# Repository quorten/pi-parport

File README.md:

## pi-parport

This is a Raspberry Pi HAT that implements a PC-style parallel port.
GPIO pins are organized as data, status, and control registers.
The HAT includes a buffer chip that converts from the GPIB 3V3 logic
to signals that conform to IEEE 1284.  A 26 pin IDC header on the
board connects to your DB25 connector.  A `parport-gpio` driver and
device tree overlay integrate the HAT with the Linux parport driver stack.

### Why?

I wanted to use a parallel port based cooled astronomy camera,
but preferred to use the compact and low-power Raspberry Pi
over a PC at the telescope.  Parallel ports are simple devices.
Why not build one?

### What works?

See [wiki](https://github.com/worlickwerx/pi-parport/wiki) for notes on some
devices, and please share your experience if you try something new.

The following limitations of this implementation may affect software and
hardware that uses the parallel port:
1) The software cannot directly read and write the x86 port addresses,
as was the custom early on.  In user space, software must use the ppdev
ioctl interface.  In the kernel, software must use the (generic)
`struct parport` operations.
2) The GPIO multiplexing/de-multiplexing and/or system call access may
impact the direct-access latency assumed by some bit-banged drivers.
On a Pi 3, user space code can toggle a parallel port line at about 250 kHz.
3) Bidirectional control pins are not currently supported.  There are
alternatives to the current buffer chip that would support this, but they
require a slightly more complicated circuit.

### Why not use a USB Parallel Port?

Many USB parallel port devices appear to Linux as a USB printer, bypassing
the parport driver stack.  If your application is a printer, go for it.

### Building the driver

For convenience, the generic parport code is duplicated in this repo,
since the Raspberry Pi Foundation does not ship the compiled modules
in the `raspberrypi-kernel` package (at least in old Raspbian
versions).  If you are intending to use a specific old version of
Raspbian, there is the shell script `get_parport_src.sh` to assist
you in getting the code from that particular version.

Clone this repo, then run the following with `${TOPDIR}` representing the
top level directory of the cloned repo:
```console
$ sudo apt install build-essential raspberrypi-kernel-headers
$ cd ${TOPDIR}/driver
$ make
make -C /lib/modules/4.19.75-v7+/build M=${TOPDIR}/driver modules
make[1]: Entering directory '/usr/src/linux-headers-4.19.75-v7+'
  CC [M]  ${TOPDIR}/driver/parport/share.o
  CC [M]  ${TOPDIR}/driver/parport/ieee1284.o
  CC [M]  ${TOPDIR}/driver/parport/ieee1284_ops.o
  CC [M]  ${TOPDIR}/driver/parport/procfs.o
  CC [M]  ${TOPDIR}/driver/parport/daisy.o
  CC [M]  ${TOPDIR}/driver/parport/probe.o
  LD [M]  ${TOPDIR}/driver/parport/parport.o
  CC [M]  ${TOPDIR}/driver/parport/lp.o
  CC [M]  ${TOPDIR}/driver/parport/ppdev.o
  CC [M]  ${TOPDIR}/driver/parport_gpio.o
  Building modules, stage 2.
  MODPOST 4 modules
  CC      ${TOPDIR}/driver/parport/lp.mod.o
  LD [M]  ${TOPDIR}/driver/parport/lp.ko
  CC      ${TOPDIR}/driver/parport/parport.mod.o
  LD [M]  ${TOPDIR}/driver/parport/parport.ko
  CC      ${TOPDIR}/driver/parport/ppdev.mod.o
  LD [M]  ${TOPDIR}/driver/parport/ppdev.ko
  CC      ${TOPDIR}/driver/parport_gpio.mod.o
  LD [M]  ${TOPDIR}/driver/parport_gpio.ko
make[1]: Leaving directory '/usr/src/linux-headers-4.19.75-v7+'
```

### Installing the Device Tree Overlay

The device tree overlay maps specific GPIO pins to their functions in
the driver.  This must be compiled and loaded:
```console
$ cd ${TOPDIR}/dts
$ make
$ sudo make install
```
The ID EEPROM stores the name of the DT Overlay to use, and the
corresponding DT Overlay will be automatically loaded on boot.  If you
will not be using an ID EEPROM, then add the following line to
`/boot/config.txt`:
```
dtoverlay=parport-gpio
```
The default drive mode of the parallel port output pins is
"totem-pole" mode, which means that a high current source is provided
for both logic level 1 and 0.  If you wish logic level 1 to be a low
current source provided by pull-up resistors, i.e. "open-drain" mode,
then you can set the following DT Overlay parameter:
```
dtoverlay=parport-gpio,hd=0
```
Note that if you are using an EEPROM, you will have to include the
full DT Overlay data within your EEPROM since you cannot simply
specify a parameter when loading by that method.

Then reboot the pi to pick up the new config.

### Installing the Modules

Install the modules to allow Linux Device Tree to automatically load
them.
```console
$ cd ${TOPDIR}/driver
$ sudo make install
```
Note that only the `parport` and `parport_gpio` base modules will
autoload, the `ppdev` and `lp` modules will still need to be specified
in `/etc/modules` or otherwise.  Also, note that you will need to
rebuild and reinstall the modules when you update your kernel version.

### Loading the Modules

If you did not install the modules, after rebooting, load the base
modules like this:
```console
$ cd ${TOPDIR}
$ sudo insmod driver/parport/parport.ko
$ sudo insmod driver/parport_gpio.ko
```
You'll see the port announce itself on the console:
```console
[4425200.988400] parport-gpio ppgpio@0: data on pins [22,23,24,10,25,9,8,11]
[4425200.988412] parport-gpio ppgpio@0: status on pins [18,17,4,3,2]
[4425200.988422] parport-gpio ppgpio@0: control on pins [26,19,6,13]
[4425200.988430] parport-gpio ppgpio@0: hd on pin 20
[4425200.988438] parport-gpio ppgpio@0: dir on pin 21
```
If you wish to set up a parallel printer:
```console
$ sudo insmod parport/lp.ko
```
If you wish to run user-space programs that use the parallel port:
```console
$ sudo insmod parport/ppdev.ko
```

### hardware

The latest hardware includes an ID EEPROM to conform with the
[Raspberry Pi HAT Specification](https://github.com/raspberrypi/hats),
and was designed with [KiCAD](https://www.kicad.org/).
As with the previous versions, the
[SN74LVC161284 19-bit bus interface with 3-state outputs](http://www.ti.com/product/SN74LVC161284) takes care of buffering and line conditioning.

Version 4 is shared on
[OSHPARK](https://oshpark.com/shared_projects/0Ioh20Gk).
See the [Bill of Materials](hardware/v4/BOM.md) for parts to place on
the board.

Populating the EEPROM and associated components on a board you're making
yourself is optional.

Check out the [test](test/) directory for some simple "smoke tests"
on your assembled pi-parport board before attaching your more
expensive equipment.

Schematics and design files for [previous versions](hardware/)
are still available for reference.

### Release

Share and enjoy!

#### Software License

SPDX-License-Identifier: GPL-2.0-or-later

#### Hardware License

SPDX-License-Identifier: CERN-OHL-1.2

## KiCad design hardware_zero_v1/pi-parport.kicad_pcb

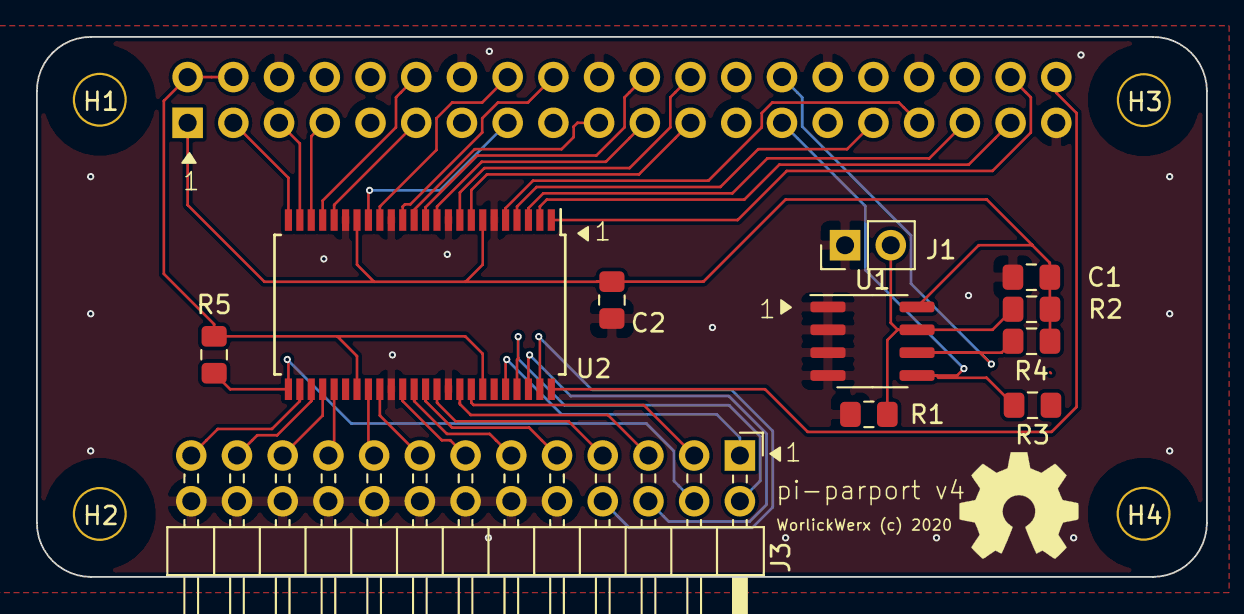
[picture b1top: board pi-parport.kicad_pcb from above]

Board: 2 copper layers, 65.0 x 30.0 mm, 16 parts (1 on the bottom side), 42 nets.

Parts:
C1, C2: 100nF; C_0805_2012Metric_Pad1.15x1.40mm_HandSolder
H1, H2, H3, H4: 3mm_Mounting_Hole; NPTH_3mm_ID
J1: CONN_01X02; PinHeader_1x02_P2.54mm_Vertical
J2: 40HAT; PinSocket_2x20_P2.54mm_Vertical
J3: Conn_02x13_Odd_Even; PinHeader_2x13_P2.54mm_Horizontal
R1: DNP; R_0805_2012Metric_Pad1.15x1.40mm_HandSolder
R2: 10K; R_0805_2012Metric_Pad1.15x1.40mm_HandSolder
R3, R4: 3.9K; R_0805_2012Metric_Pad1.15x1.40mm_HandSolder
R5: 1.4K; R_0805_2012Metric_Pad1.15x1.40mm_HandSolder
U1: CAT24C32; SOIC-8_3.9x4.9mm_P1.27mm
U2: SN74LVC161284DLR; SSOP-48_7.5x15.9mm_P0.635mm

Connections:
+3V3: C1.1, C2.1, J2.1, R2.2, R3.1, R4.1, U1.8, U2.7, U2.18
+5V: J2.2, J2.4, R5.2, U2.31, U2.42
/CONTROL0: J3.1, U2.44
/CONTROL1: J3.2, U2.45
/CONTROL2: J3.6, U2.46
/CONTROL3: J3.8, U2.47
/DATA0: J3.3, U2.41
/DATA1: J3.5, U2.40
/DATA2: J3.7, U2.38
/DATA3: J3.9, U2.37
/DATA4: J3.11, U2.36
/DATA5: J3.13, U2.35
/DATA6: J3.15, U2.33
/DATA7: J3.17, U2.32
/GPIO2: J2.3, U2.24
/GPIO3: J2.5, U2.23
/GPIO4: J2.7, U2.22
/GPIO6: J2.31, U2.4
/GPIO8: J2.24, U2.9
/GPIO9: J2.21, U2.11
/GPIO10: J2.19, U2.13
/GPIO11: J2.23, U2.8
/GPIO13: J2.33, U2.5
/GPIO17: J2.11, U2.20
/GPIO18: J2.12, U2.21
/GPIO19: J2.35, U2.3
/GPIO20: J2.38, U2.1
/GPIO21: J2.40, U2.48
/GPIO22: J2.15, U2.17
/GPIO23: J2.16, U2.16
/GPIO24: J2.18, U2.14
/GPIO25: J2.22, U2.12
/GPIO26: J2.37, U2.2
/ID_SC_EEPROM: J2.28, R4.2, U1.6
/ID_SD_EEPROM: J2.27, R3.2, U1.5
/STATUS3: J3.4, R5.1, U2.25
/STATUS4: J3.25, U2.26
/STATUS5: J3.23, U2.27
/STATUS6: J3.19, U2.29
/STATUS7: J3.21, U2.28
GND: C1.2, C2.2, J1.1, J2.6, J2.9, J2.14, J2.20, J2.25, J2.30, J2.34, J2.39, J3.10, J3.12, J3.14, J3.16, J3.18, J3.20, J3.22, J3.24, J3.26, R1.2, U1.1, U1.2, U1.3, U1.4, U2.6, U2.10, U2.15, U2.19, U2.34, U2.39
unnamed: J1.2, R1.1, R2.1, U1.7

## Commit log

2020-07-24 hardware_v4: add bypass capacitors, reroute traces
    Do not route trace under resistor R5. Move U2 upward to facilitate
    rerouting this trace without adding more vias.
    Also make sure footprints between schematic and PCB are in sync.
    Update BOM with new parts.
    Hardware version needs to be bumped due to PCB changes. Version numbers
    in schematic and PCB source changed, new files will need to be generated
2020-07-25 Clone v4 hardware to start RPi Zero HAT.
2020-07-25 First run at RPi Zero form factor.
2020-11-07 driver: Additional control pin support, ppdev control over HD.
2024-10-20 Add limitation note to README.md on bidirectional control pins.
    Bidirectional control pins are not currently supported, but we have
    been investigating support for this.
2024-10-20 Clarify that bidirectional data is supported.

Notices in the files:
hardware_zero_v1/pi-parport.kicad_pcb:
WorlickWerx (c) 2020
